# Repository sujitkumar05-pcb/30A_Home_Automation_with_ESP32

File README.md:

# 30A_Home_Automation_with_ESP32

## 1. Project Overview

30A Home Automation with ESP32 is a high-power IoT control system designed to safely switch electrical loads up to 30A. It uses the ESP32 for Wi-Fi–based remote control and automation. The complete schematic, PCB layout, and 3D design were developed in KiCad, with a strong focus on electrical isolation, proper track width, and safety for real-world applications.

-----

## 2. Key Learning Objectives

Understanding high-current (30A) PCB design and safety considerations

Practical experience with ESP32-based IoT hardware development

Schematic capture and multi-layer PCB layout using KiCad

Track width calculation, creepage & clearance implementation

Hardware testing, debugging, and design verification

Generating manufacturing (Gerber) and 3D output files

-----

## 3. Tools & Software Used
- **KiCad EDA**
  - Schematic Editor  
  - PCB Layout Editor  
  - 3D Viewer
 
 ---

## 4. Project Files
- Schematic design files (`.kicad_sch`)  
- PCB layout files (`.kicad_pcb`)  
- 3D render images  
- Manufacturing-ready Gerber files  

---

## 5. Block-Level Working Explanation

The system is powered by an AC mains supply, which is converted to a regulated DC voltage using a power supply module to safely operate the control circuitry. The ESP32 acts as the main controller, receiving user commands via Wi-Fi from a mobile or web application.

Based on these commands, the ESP32 drives an isolated switching stage (relay/contactor or solid-state device), ensuring safe separation between low-voltage control and high-current load circuits. The switching stage controls the connected 30A electrical load, turning it ON or OFF as required.

Protection components such as fuses, flyback diodes, and filtering circuits are included to enhance safety, reliability, and noise immunity. The system provides reliable remote control while maintaining electrical isolation and thermal safety.

## 6. Bill of Materials (BOM)
| Reference | Qty | Value / Part No.      | Footprint            | Datasheet / Notes |
| --------- | --- | --------------------- | -------------------- | ----------------- |
| C1        | 1   | 10 µF                 | C_0805_2012Metric    | –                 |
| C2        | 1   | 22 µF                 | C_0805_2012Metric    | –                 |
| D1, D4    | 2   | LED                   | LED_0805_2012Metric  | –                 |
| D2, D3    | 2   | 1N4148                | DO-35 (THT)          | Nexperia          |
| H1–H4     | 4   | Mounting Hole M2.5    | MountingHole_2.7 mm  | Excluded from BOM |
| J1        | 1   | 1×4 Pin Header        | PinHeader_2.54 mm    | –                 |
| J2        | 1   | 4-Pin Screw Terminal  | Phoenix MSTB 5.08 mm | –                 |
| J3        | 1   | 3-Pin Screw Terminal  | Phoenix MSTB 5.08 mm | –                 |
| K1        | 1   | RAYEX-L90AS Relay     | Relay_SPST_THT       | RAYEX             |
| K2        | 1   | PR13-5V-450-1C Relay  | Relay THT            | –                 |
| PS1       | 1   | HLK-PM01 AC–DC Module | Hi-Link_HLK-PMxx     | Hi-Link           |
| Q1, Q2    | 2   | S8050 Transistor      | TO-92                | –                 |
| R1–R6     | 6   | 1 kΩ                  | R_0805_2012Metric    | –                 |
| R7, R8    | 2   | 10 kΩ                 | R_0805_2012Metric    | –                 |
| SW1, SW2  | 2   | Push Button Switch    | 6 mm THT             | –                 |
| U1        | 1   | ESP32-WROOM-32        | RF_Module            | Espressif         |
| U2, U3    | 2   | PC817 Optocoupler     | DIP-4                | –                 |
| U4        | 1   | AMS1117-3.3           | TO-252-3             | –                 |

## 7. Images & Renders

- **Schematic**

- **PCB Layout**

- **3D View**

## 8. Disclaimer
This project is intended for educational and experimental purposes only. It involves high-voltage and high-current (up to 30A) circuits, which can be dangerous if handled improperly. The author is not responsible for any damage, injury, or loss resulting from the use, modification, or implementation of this design.
Users are advised to follow proper electrical safety standards, use appropriate protective components, and verify the design thoroughly before real-world deployment

---

## 9. Author
- **Name:** Er.SUJIT KUMAR
- **Toolchain:** KiCad EDA

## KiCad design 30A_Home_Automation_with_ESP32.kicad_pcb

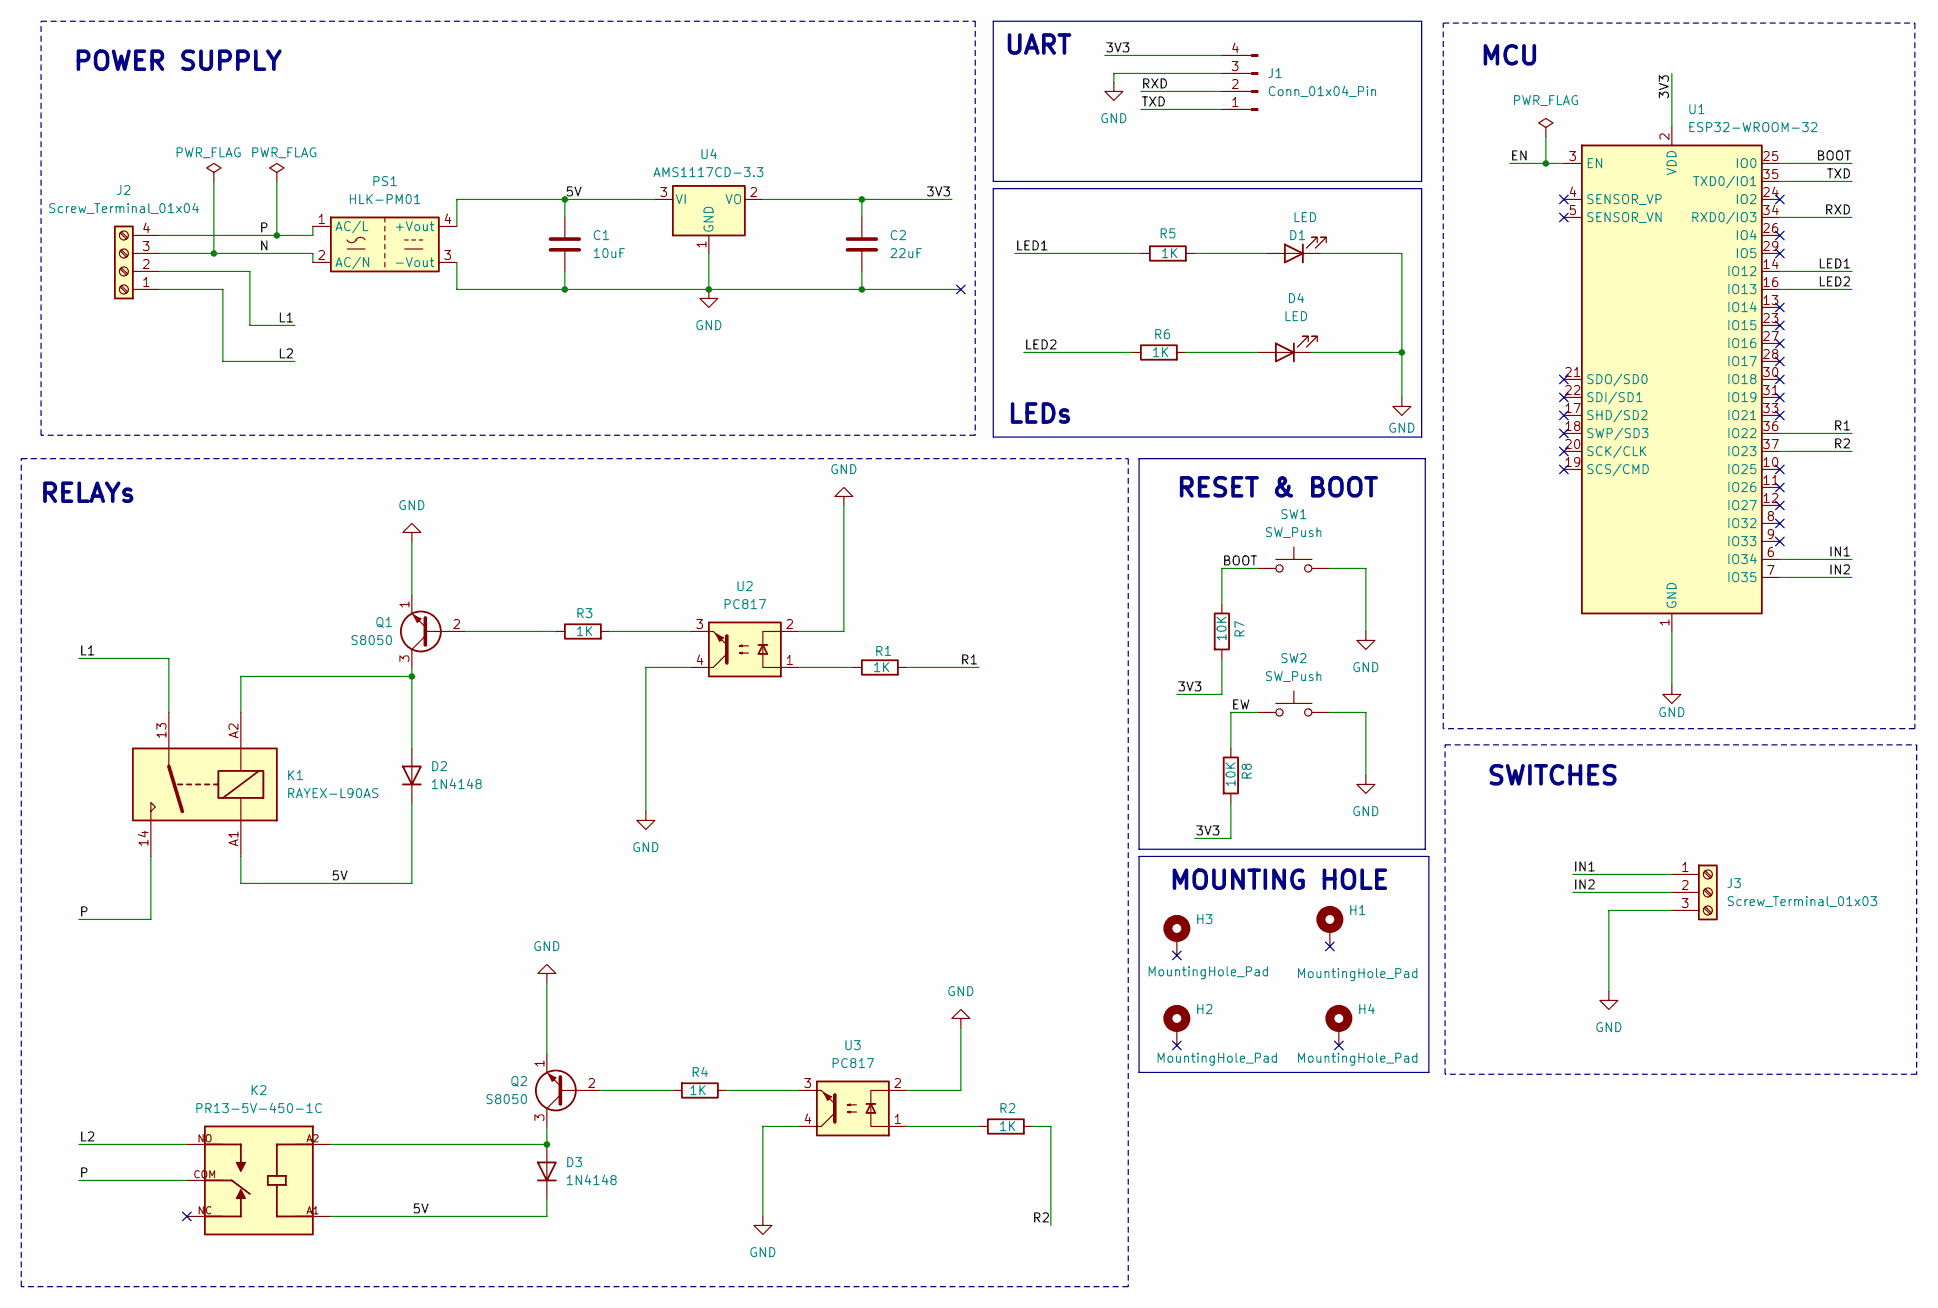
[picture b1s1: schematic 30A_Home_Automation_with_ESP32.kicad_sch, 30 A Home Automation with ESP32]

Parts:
C1: 10uF; C_0805_2012Metric
C2: 22uF; C_0805_2012Metric
D1, D4: LED; LED_0805_2012Metric
D2, D3: 1N4148; D_DO-35_SOD27_P7.62mm_Horizontal
H1, H2, H3, H4: MountingHole_Pad; MountingHole_2.7mm_M2.5_Pad_Via
J1: Conn_01x04_Pin; PinHeader_1x04_P2.54mm_Vertical
J2: Screw_Terminal_01x04; PhoenixContact_MSTBVA_2,5_4-G-5,08_1x04_P5.08mm_Vertical
J3: Screw_Terminal_01x03; PhoenixContact_MSTBVA_2,5_3-G-5,08_1x03_P5.08mm_Vertical
K1: RAYEX-L90AS; Relay_SPST_RAYEX-L90AS
K2: PR13-5V-450-1C; RELAY_PR13-5V-450-1C; PARTREV 1.0
PS1: HLK-PM01; Converter_ACDC_Hi-Link_HLK-PMxx
Q1, Q2: S8050; TO-92_Inline
R1, R2, R3, R4, R5, R6: 1K; R_0805_2012Metric
R7, R8: 10K; R_0805_2012Metric
SW1, SW2: SW_Push; SW_PUSH_6mm
U1: ESP32-WROOM-32
U2, U3: PC817; DIP-4_W7.62mm
U4: AMS1117CD-3.3; TO-252-3_TabPin2

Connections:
/3V3: C2.1, J1.4, R7.2, R8.2, U1.2 (VDD), U4.2 (VO)
/5V: C1.1, D2.1 (K), D3.1 (K), K1.A1, K2.A1, PS1.4 (+Vout), U4.3 (VI)
/BOOT: R7.1, SW1.1, U1.25 (IO0)
/EN: U1.3 (EN)
/EW: R8.1, SW2.1
/IN1: J3.1, U1.6 (IO34)
/IN2: J3.2, U1.7 (IO35)
/L1: J2.2, K1.13
/L2: J2.1, K2.NO
/LED1: R5.1, U1.14 (IO12)
/LED2: R6.1, U1.16 (IO13)
/N: J2.3, PS1.2 (AC/N)
/P: J2.4, K1.14, K2.COM, PS1.1 (AC/L)
/R1: R1.2, U1.36 (IO22)
/R2: R2.2, U1.37 (IO23)
/RXD: J1.2, U1.34 (RXD0/IO3)
/TXD: J1.1, U1.35 (TXD0/IO1)
GND: C1.2, C2.2, D1.1 (K), D4.1 (K), J1.3, J3.3, PS1.3 (-Vout), Q1.1 (E), Q2.1 (E), SW1.2, SW2.2, U1.1 (GND), U1.15 (GND), U1.38 (GND), U1.39 (GND), U2.2, U2.4, U3.2, U3.4, U4.1 (GND)
unnamed: D1.2 (A), R5.2
unnamed: D2.2 (A), K1.A2, Q1.3 (C)
unnamed: D3.2 (A), K2.A2, Q2.3 (C)
unnamed: D4.2 (A), R6.2
unnamed: Q1.2 (B), R3.1
unnamed: Q2.2 (B), R4.2
unnamed: R1.1, U2.1
unnamed: R2.1, U3.1
unnamed: R3.2, U2.3
unnamed: R4.1, U3.3

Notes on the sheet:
SWITCHES
LEDs
POWER SUPPLY
MOUNTING HOLE
RELAYs
MCU
UART
RESET & BOOT

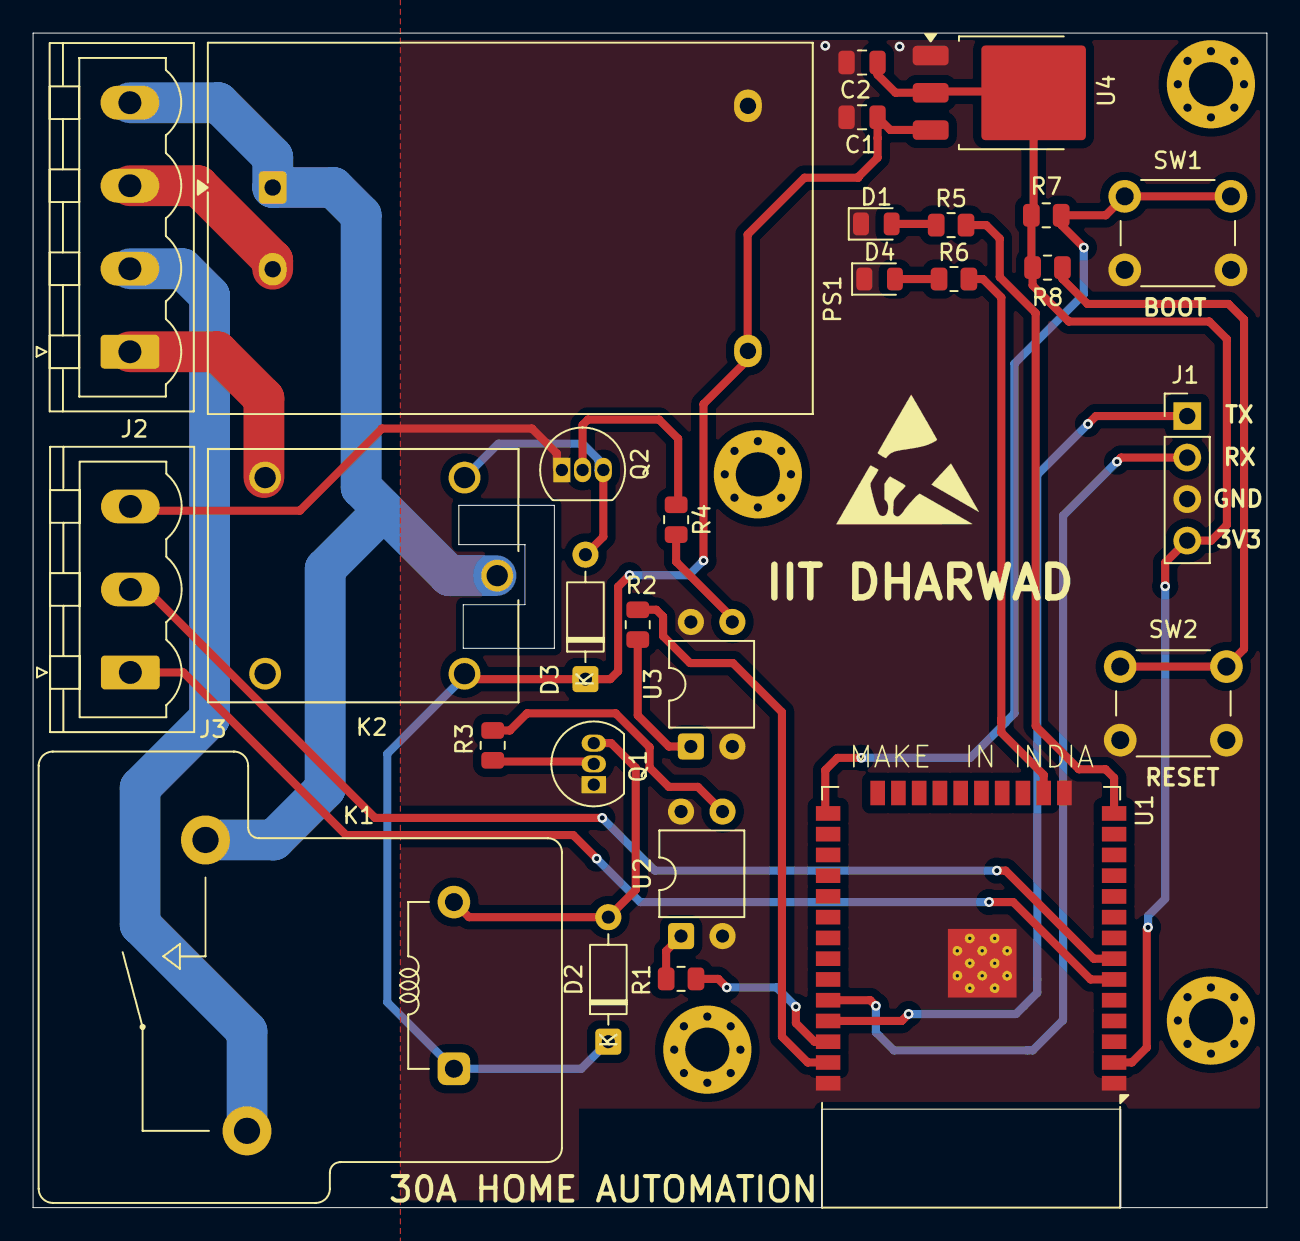
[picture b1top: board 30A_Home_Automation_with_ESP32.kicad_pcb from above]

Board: 2 copper layers, 75.5 x 71.9 mm, 32 parts (0 on the bottom side), 27 nets.
